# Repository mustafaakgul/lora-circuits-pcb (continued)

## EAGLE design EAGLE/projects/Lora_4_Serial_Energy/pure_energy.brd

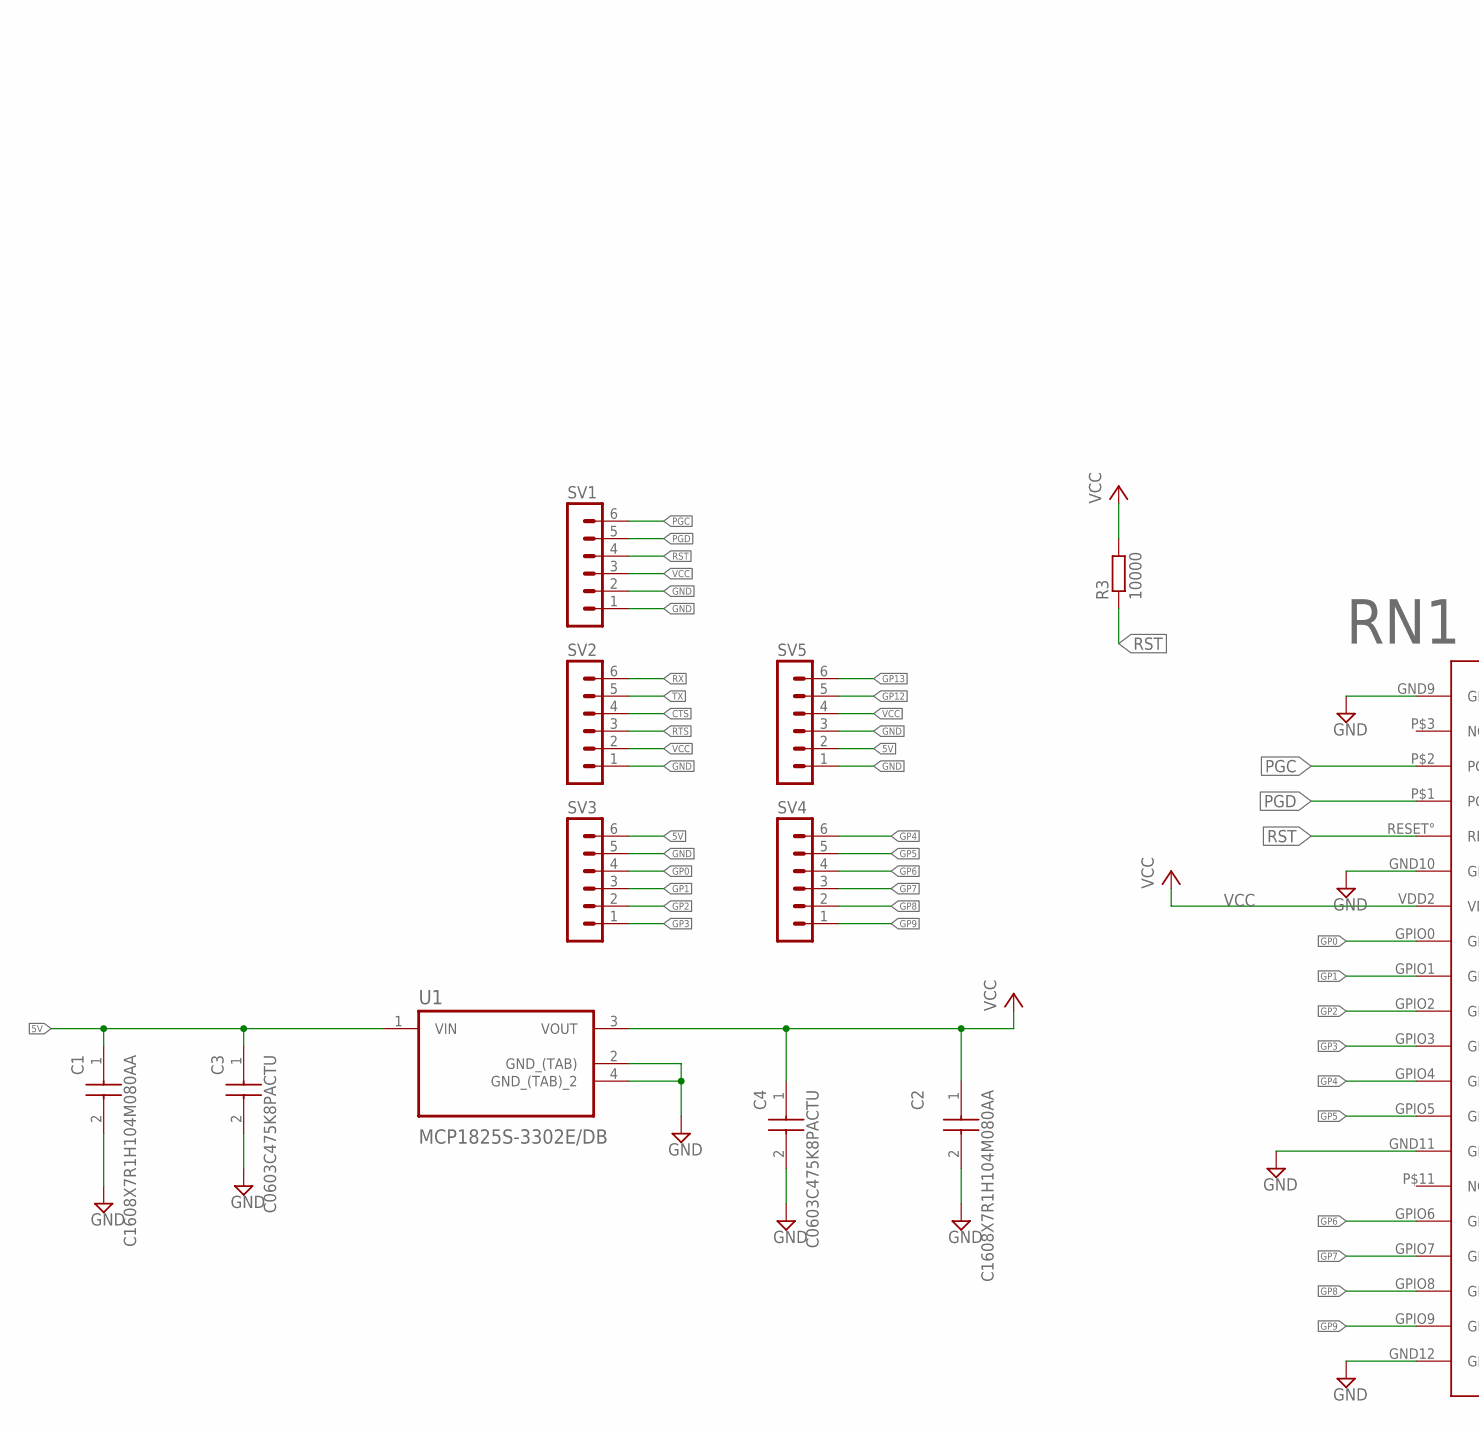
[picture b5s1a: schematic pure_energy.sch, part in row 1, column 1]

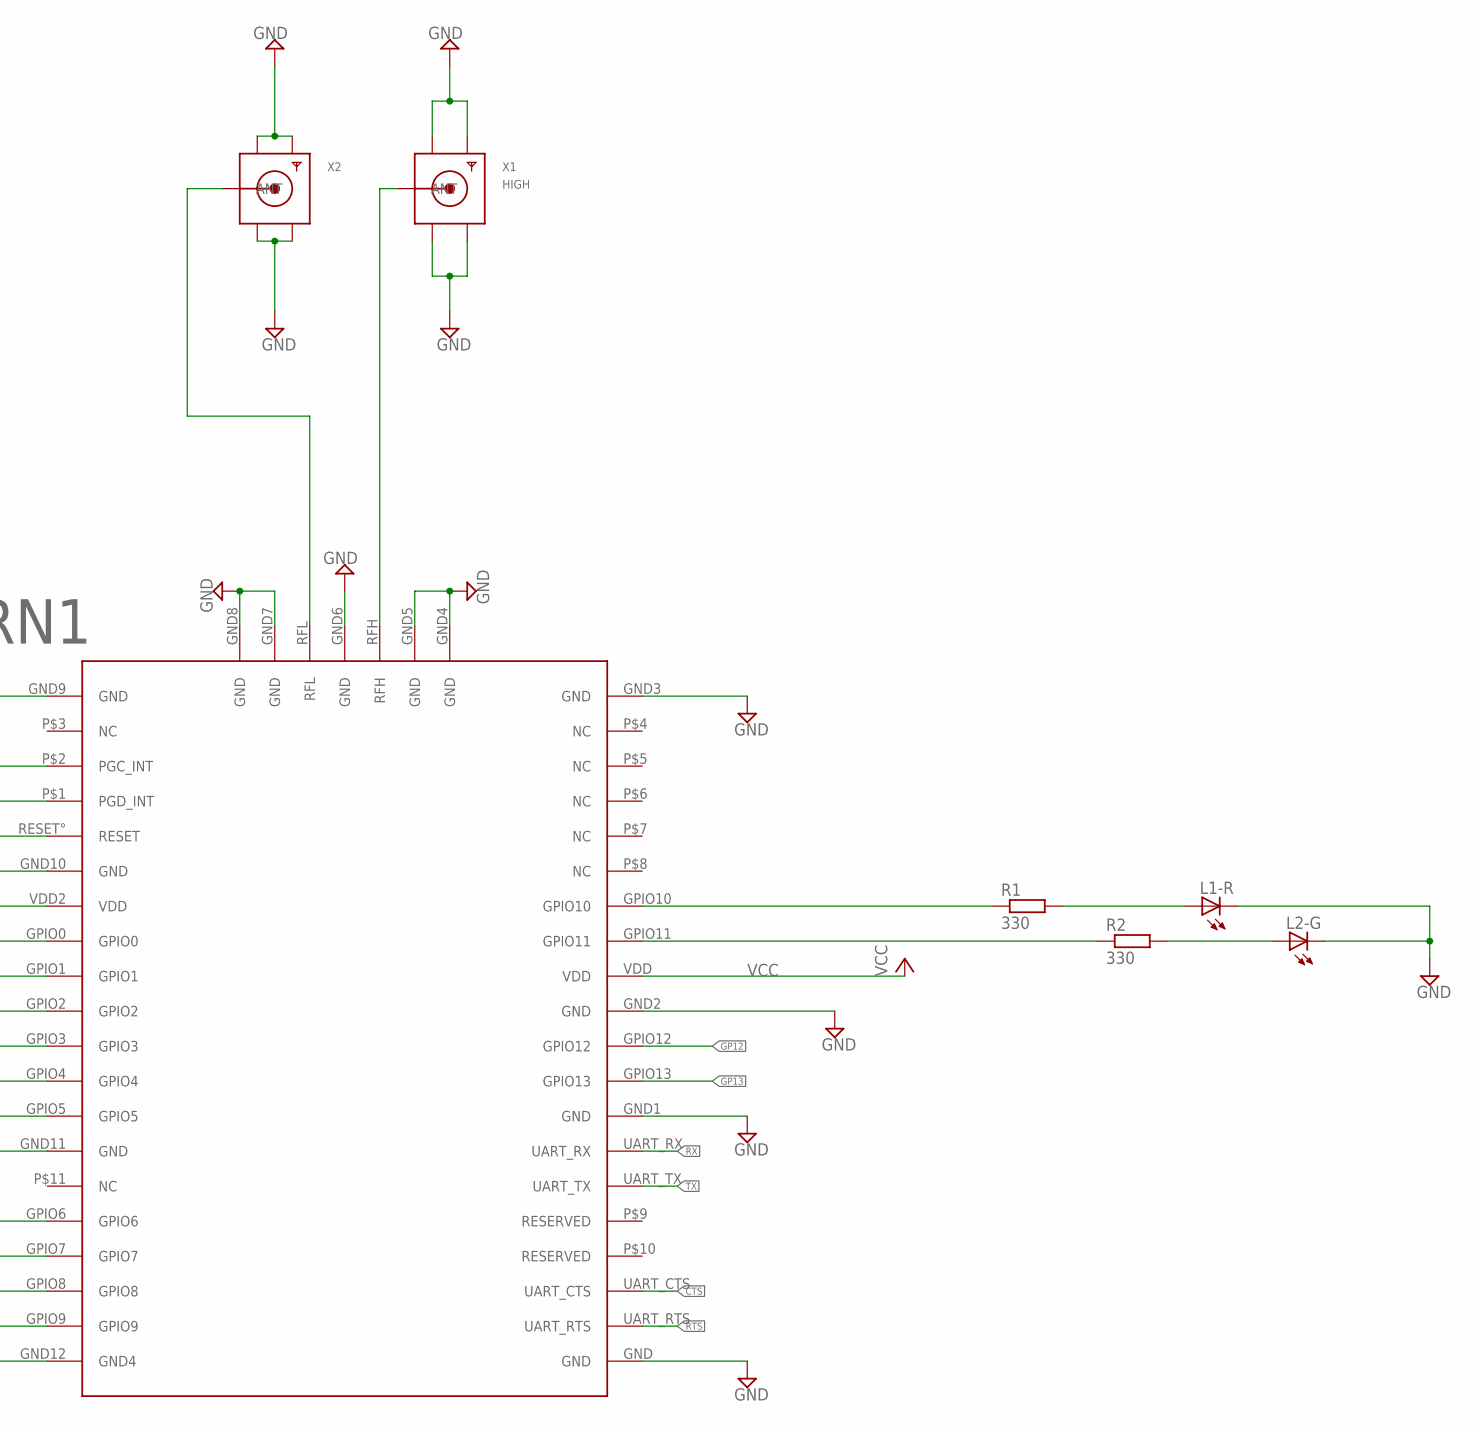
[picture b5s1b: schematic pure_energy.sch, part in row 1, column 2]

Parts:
C1, C2: C1608X7R1H104M080AA; CAPC1608X80N
C3, C4: C0603C475K8PACTU; CAPC1608X85N
L1-R, L2-G: LEDCHIP-LED0603; CHIP-LED0603
R1, R2: 330; R0603
R3: 10000; R0603
RN1: NEW_RN2483
SV1, SV2, SV3, SV4, SV5: MA06-1
U1: MCP1825S-3302E/DB; SOT230P700X180-4N
X1: HIGH; SMA_EDGELAUNCH
X2: SMACONNECTOR_EDGE; SMA_EDGELAUNCH

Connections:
5V: C1.1, C3.1 (C1), SV3.6, SV5.2, U1.1 (VIN)
CTS: RN1.UART_CTS, SV2.4
GND: C1.2, C2.2, C3.2 (C2), C4.2 (C2), L1-R.C, L2-G.C, RN1.GND, RN1.GND1 (GND), RN1.GND2 (GND), RN1.GND3 (GND), RN1.GND4 (GND), RN1.GND5 (GND), RN1.GND6 (GND), RN1.GND7 (GND), RN1.GND8 (GND), RN1.GND9 (GND), RN1.GND10 (GND), RN1.GND11 (GND), RN1.GND12 (GND4), SV1.1, SV1.2, SV2.1, SV3.5, SV5.1, SV5.3, U1.2 (GND_(TAB)), U1.4 (GND_(TAB)_2), X1.GND@1 (GND4), X1.GND@2 (GND3), X1.GND@3 (GND2), X1.GND@4 (GND1), X2.GND@1 (GND4), X2.GND@2 (GND3), X2.GND@3 (GND2), X2.GND@4 (GND1)
GP0: RN1.GPIO0, SV3.4
GP1: RN1.GPIO1, SV3.3
GP2: RN1.GPIO2, SV3.2
GP3: RN1.GPIO3, SV3.1
GP4: RN1.GPIO4, SV4.6
GP5: RN1.GPIO5, SV4.5
GP6: RN1.GPIO6, SV4.4
GP7: RN1.GPIO7, SV4.3
GP8: RN1.GPIO8, SV4.2
GP9: RN1.GPIO9, SV4.1
GP12: RN1.GPIO12, SV5.5
GP13: RN1.GPIO13, SV5.6
unnamed: RN1.RFL, X2.P (ANT)
unnamed: R1.1, RN1.GPIO10
unnamed: R2.1, RN1.GPIO11
unnamed: L1-R.A, R1.2
unnamed: L2-G.A, R2.2
unnamed: RN1.RFH, X1.P (ANT)
PGC: RN1.P$2 (PGC_INT), SV1.6
PGD: RN1.P$1 (PGD_INT), SV1.5
RST: R3.1, RN1.RESET° (RESET), SV1.4
RTS: RN1.UART_RTS, SV2.3
RX: RN1.UART_RX, SV2.6
TX: RN1.UART_TX, SV2.5
VCC: C2.1, C4.1 (C1), R3.2, RN1.VDD, RN1.VDD2 (VDD), SV1.3, SV2.2, SV5.4, U1.3 (VOUT)

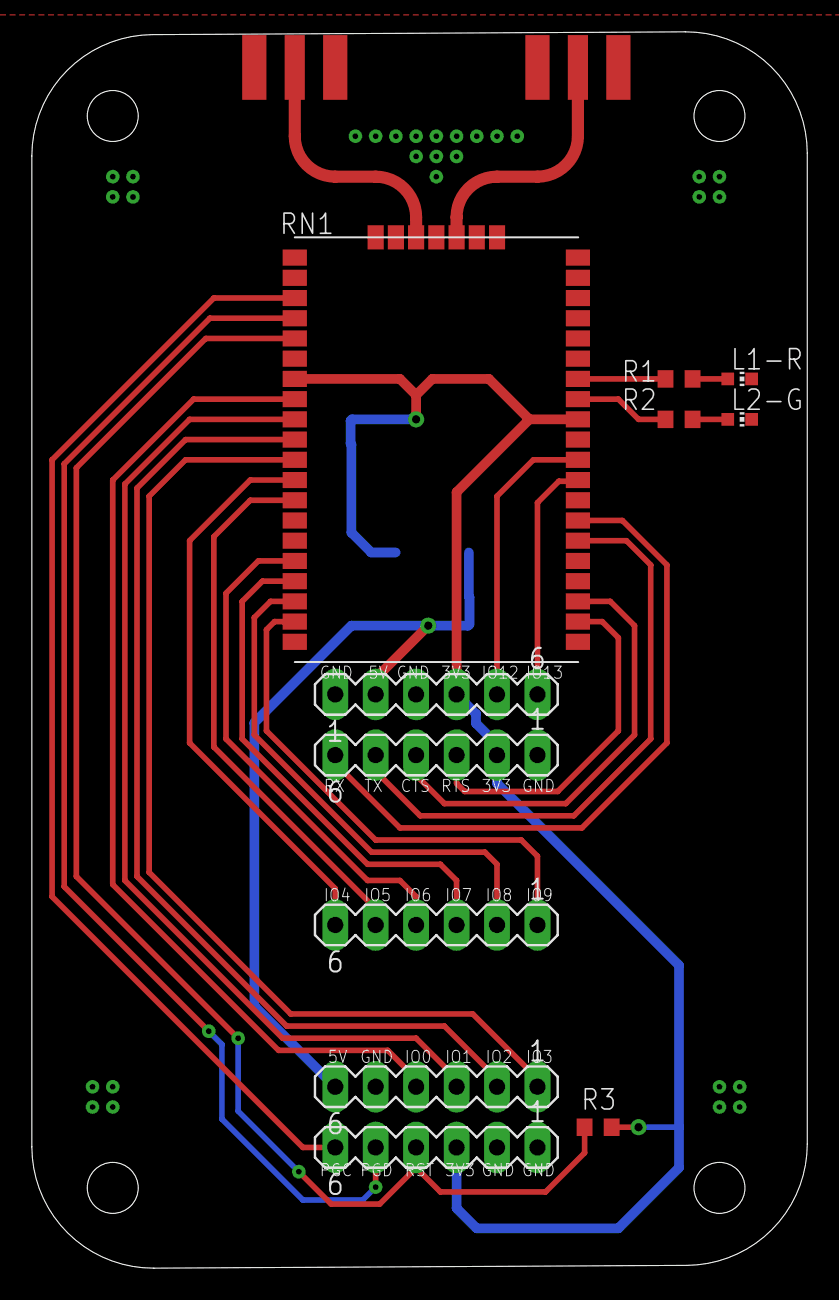
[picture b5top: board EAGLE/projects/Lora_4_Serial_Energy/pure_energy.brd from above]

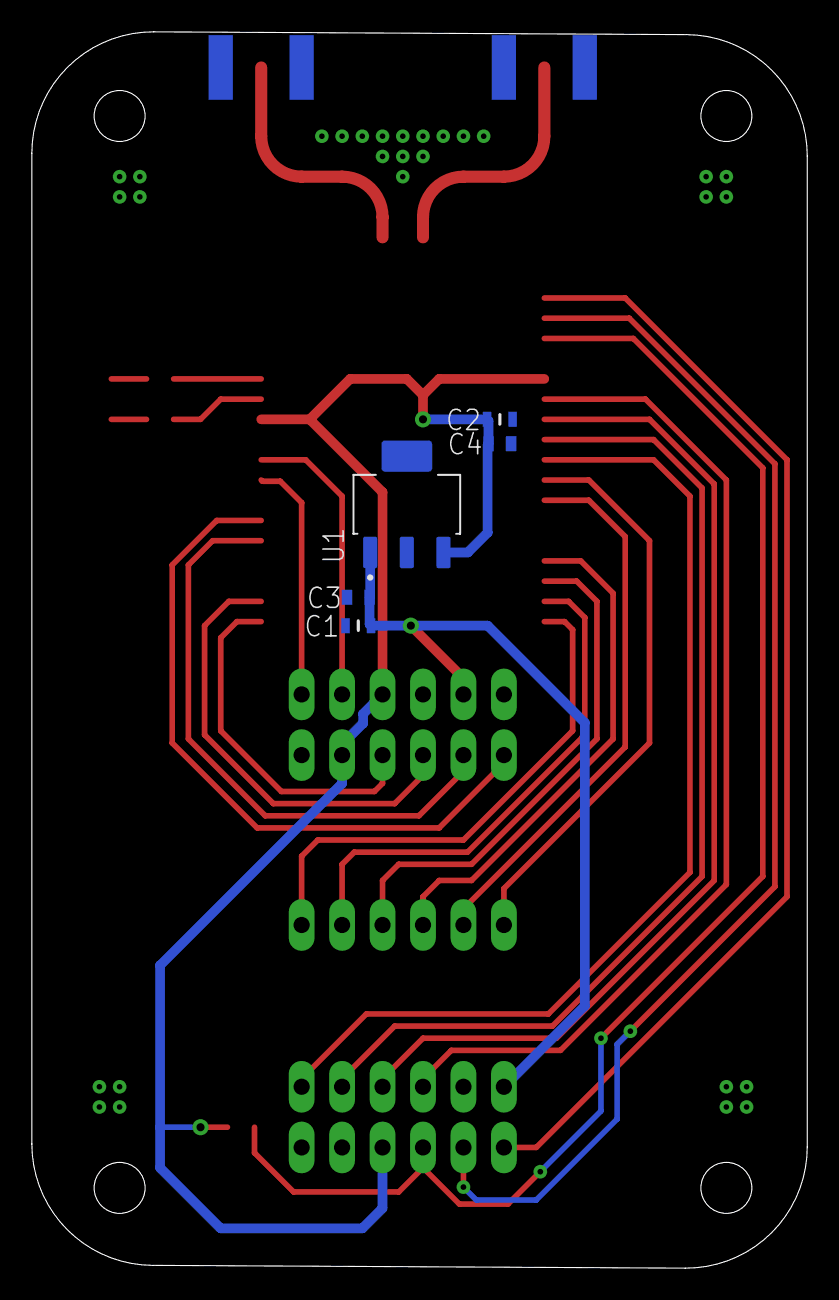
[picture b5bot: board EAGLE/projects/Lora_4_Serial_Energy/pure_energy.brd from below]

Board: 2 copper layers, 48.7 x 77.6 mm, 18 parts (5 on the bottom side), 28 nets.

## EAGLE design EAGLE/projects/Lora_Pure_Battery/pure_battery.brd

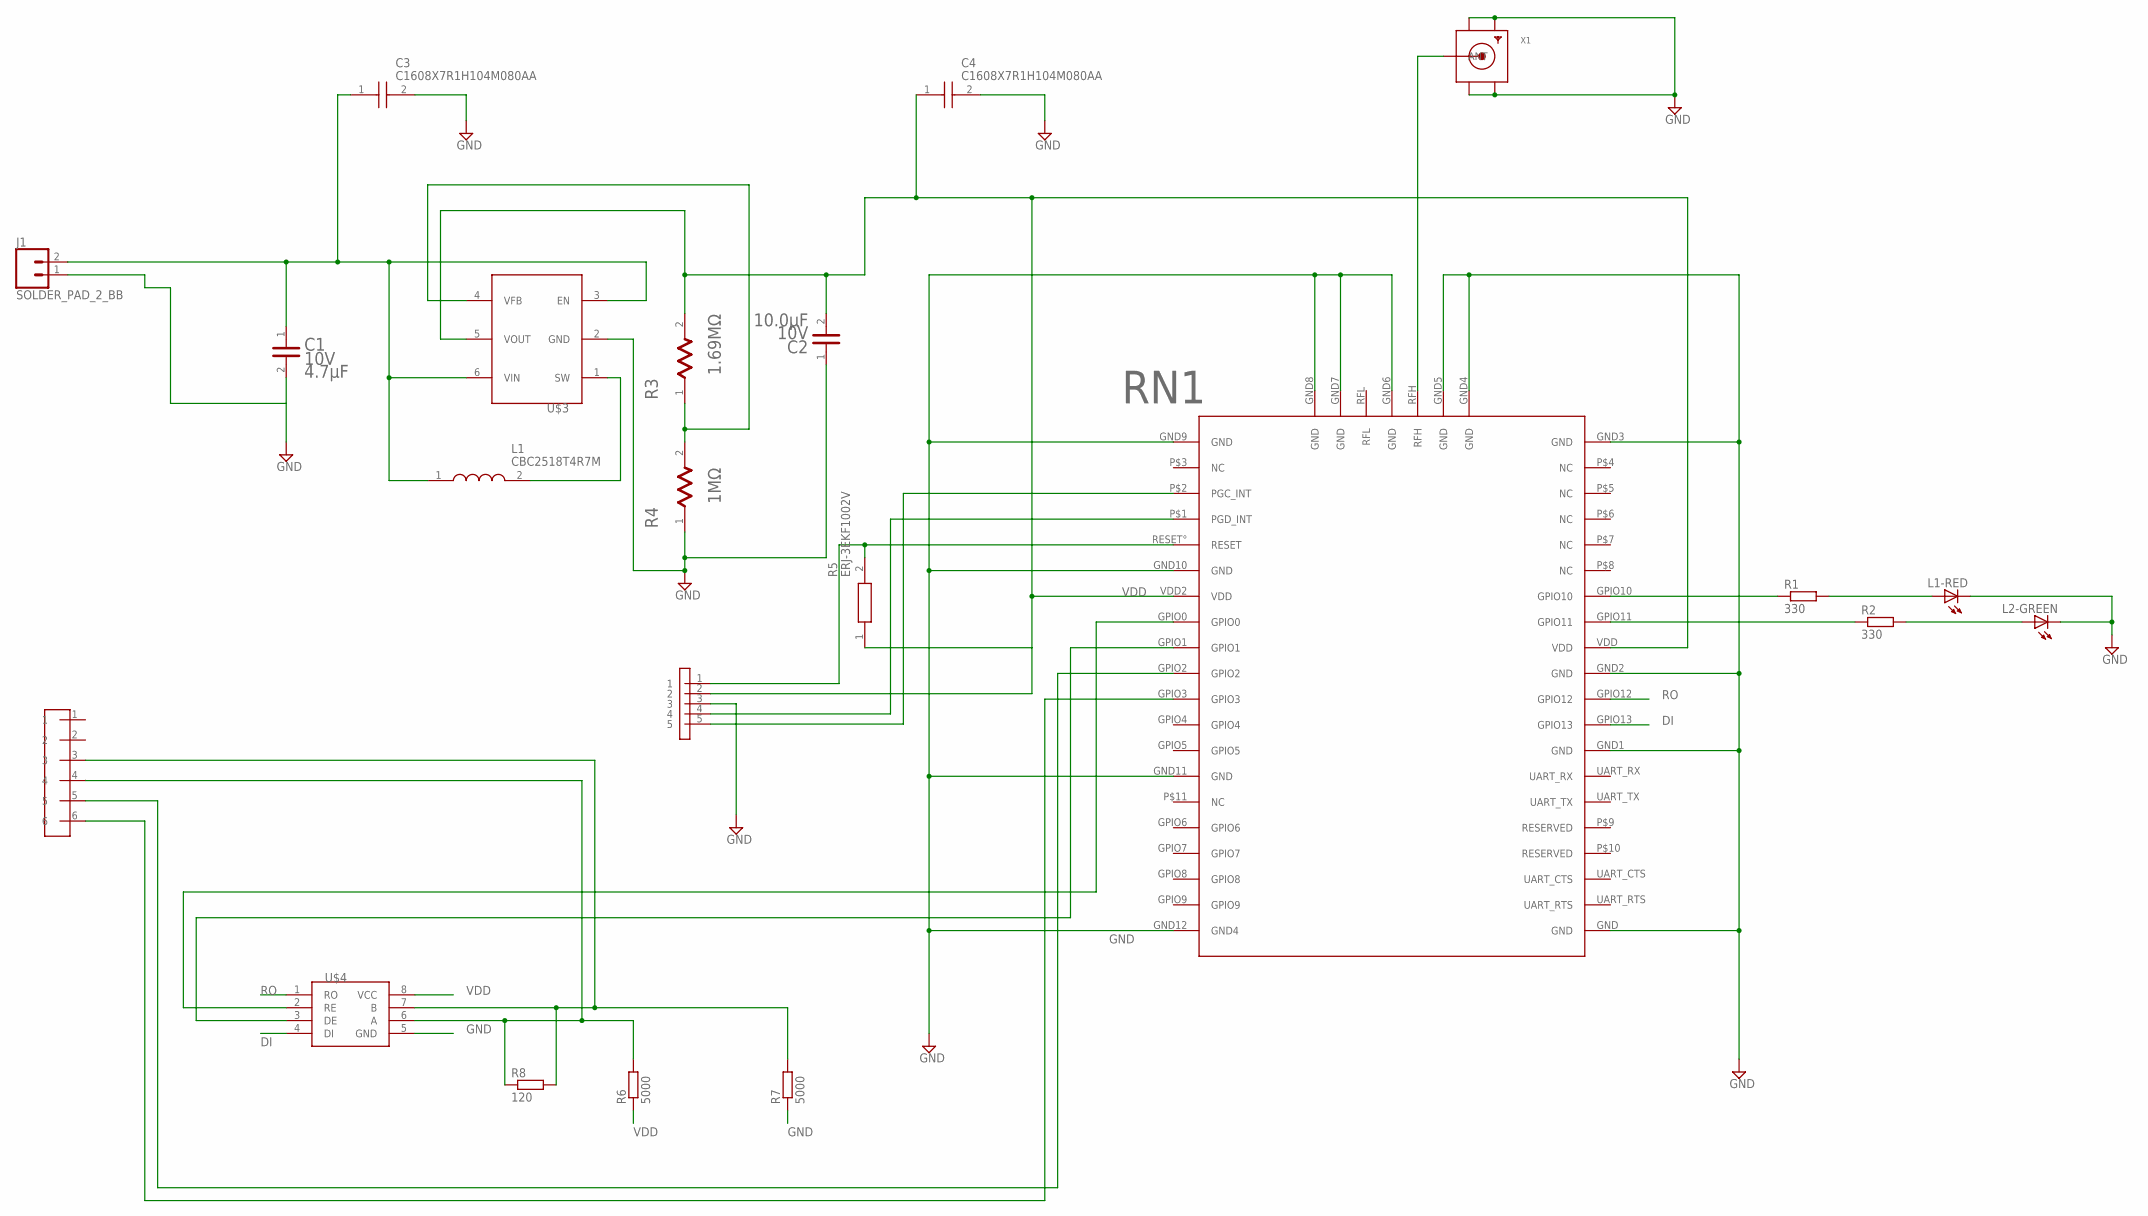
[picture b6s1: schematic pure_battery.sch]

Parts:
C1: KEMET_C0603C475K8PACTUKEMET_C0603C475K8PACTU_0_0; KEMET_C0603C475K8PACTU_0
C2: TDK_C1608X5R1A106M080ACTDK_C1608X5R1A106M080AC_0_0; TDK_C1608X5R1A106M080AC_0
C3, C4: C1608X7R1H104M080AA; CAPC1608X80N
J1: SOLDER_PAD_2_BB; SOLDER_PAD_2
L1: CBC2518T4R7M; INDC2518X200N
L1-RED, L2-GREEN: LEDCHIP-LED0603; CHIP-LED0603
R1, R2: 330; R0603
R3: VISHAY_CRCW06031M69FKEAVISHAY_CRCW06031M69FKEA_0_1; VISHAY_CRCW06031M69FKEA_1
R4: STACKPOLE_RMCF0603FT1M00STACKPOLE_RMCF0603FT1M00_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; STACKPOLE_RMCF0603FT1M00_1
R5: ERJ-3EKF1002V; RESC1608X55N
R6, R7: 5000; R0805
R8: 120; R0805
RN1: NEW_RN2483
U$1: CONNECTOR62; CONNECTOR6
U$2: ICSP52; ICSP
U$3: MCP16252
U$4: AMD3485E
X1: SMACONNECTOR_EDGE; SMA_EDGELAUNCH

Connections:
DI: RN1.GPIO13, U$4.4 (DI)
GND: C1.2, C2.1, C3.2, C4.2, J1.1, L1-RED.C, L2-GREEN.C, R4.1, R7.1, RN1.GND, RN1.GND1 (GND), RN1.GND2 (GND), RN1.GND3 (GND), RN1.GND4 (GND), RN1.GND5 (GND), RN1.GND6 (GND), RN1.GND7 (GND), RN1.GND8 (GND), RN1.GND9 (GND), RN1.GND10 (GND), RN1.GND11 (GND), RN1.GND12 (GND4), U$2.3, U$3.2 (GND), U$4.5 (GND), X1.GND@1 (GND4), X1.GND@2 (GND3), X1.GND@3 (GND2), X1.GND@4 (GND1)
unnamed: R1.1, RN1.GPIO10
unnamed: L1-RED.A, R1.2
unnamed: C1.1, C3.1, J1.2, L1.1, U$3.3 (EN), U$3.6 (VIN)
unnamed: R2.1, RN1.GPIO11
unnamed: L2-GREEN.A, R2.2
unnamed: RN1.P$2 (PGC_INT), U$2.5
unnamed: L1.2, U$3.1 (SW)
unnamed: R3.1, R4.2, U$3.4 (VFB)
unnamed: RN1.P$1 (PGD_INT), U$2.4
unnamed: RN1.GPIO0, U$4.2 (RE)
unnamed: R5.2, RN1.RESET° (RESET), U$2.1
unnamed: RN1.RFH, X1.P (ANT)
unnamed: R7.2, R8.2, U$1.3, U$4.7 (B)
unnamed: R6.2, R8.1, U$1.4, U$4.6 (A)
unnamed: RN1.GPIO1, U$4.3 (DE)
unnamed: RN1.GPIO2, U$1.5
unnamed: RN1.GPIO3, U$1.6
RO: RN1.GPIO12, U$4.1 (RO)
VDD: C2.2, C4.1, R3.2, R5.1, R6.1, RN1.VDD, RN1.VDD2 (VDD), U$2.2, U$3.5 (VOUT), U$4.8 (VCC)

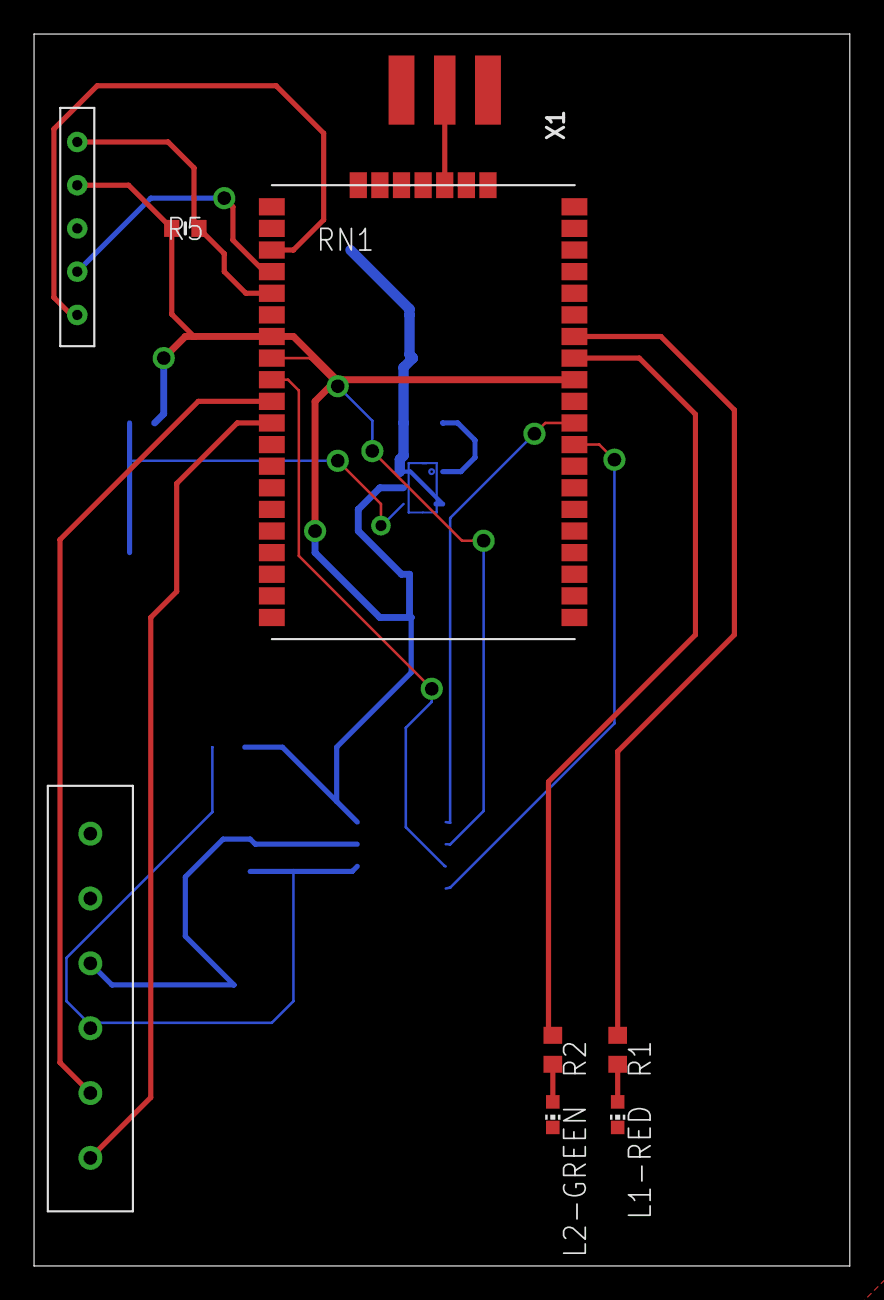
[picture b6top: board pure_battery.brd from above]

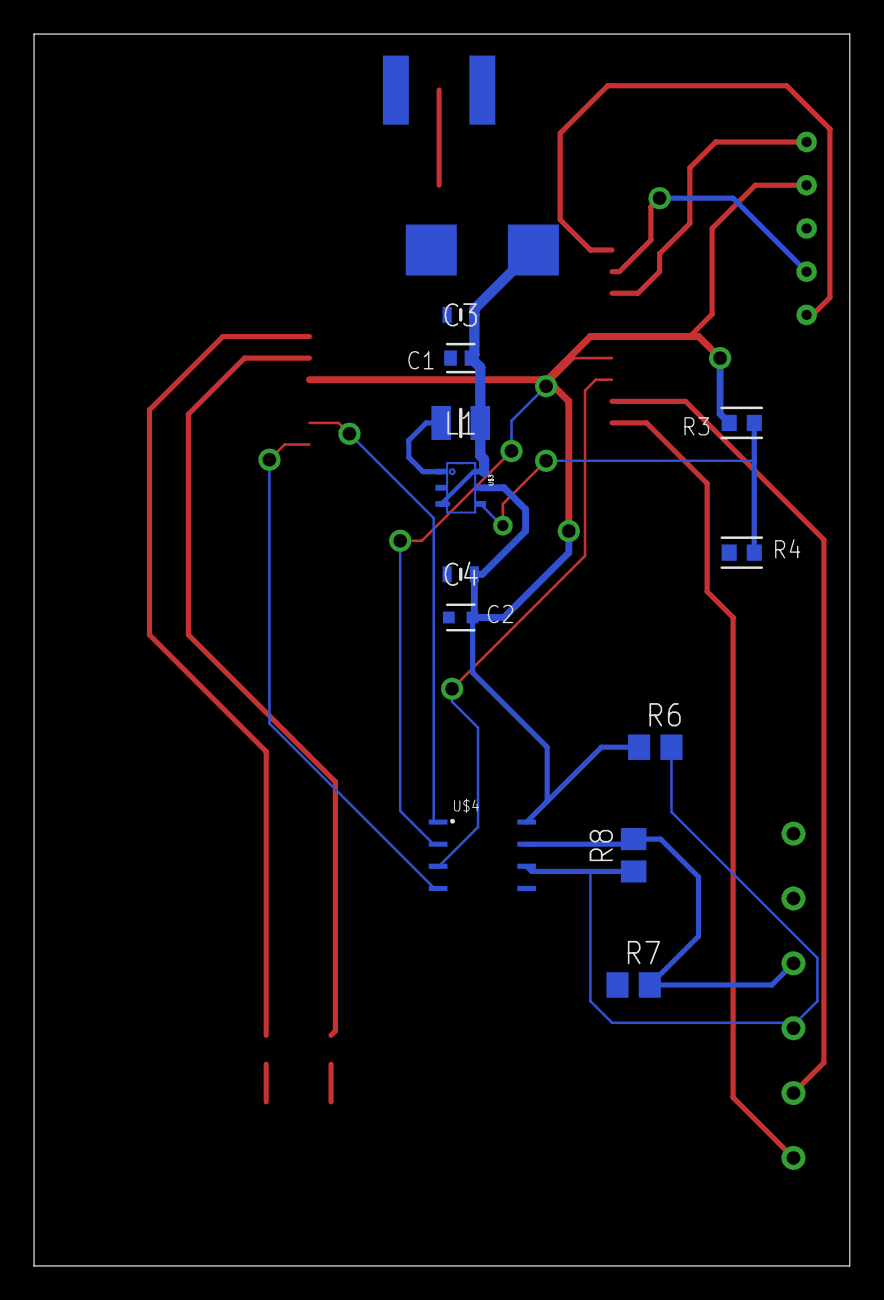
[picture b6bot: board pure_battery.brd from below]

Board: 2 copper layers, 47.9 x 72.4 mm, 22 parts (13 on the bottom side), 21 nets.

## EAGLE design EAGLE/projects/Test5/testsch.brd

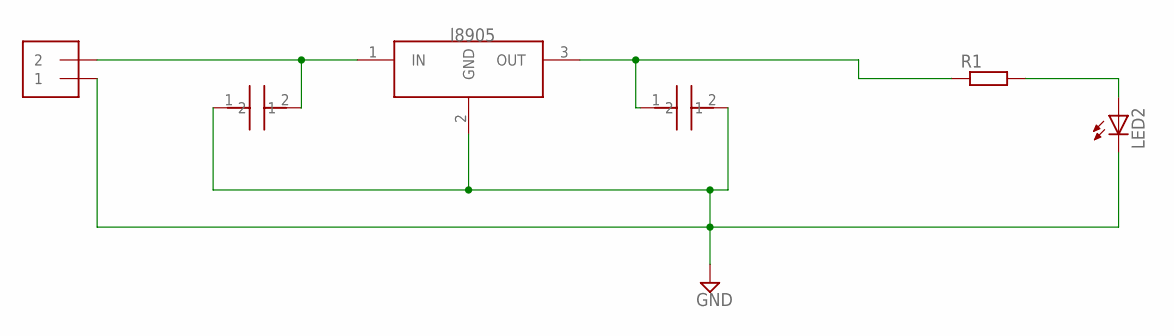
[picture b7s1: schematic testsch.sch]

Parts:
J1: 1X2-3.5MM
LED2: LEDSMT1206; 1206
R1: R-EU_M1206; M1206
U$1: L7805TESTA; L7805
U$2, U$3: 0.33UF_CUSTOM; C1206

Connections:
GND: J1.1, LED2.C, U$1.2 (GND), U$2.1, U$3.2
unnamed: J1.2, U$1.1 (IN), U$2.2
unnamed: LED2.A, R1.2
unnamed: R1.1, U$1.3 (OUT), U$3.1

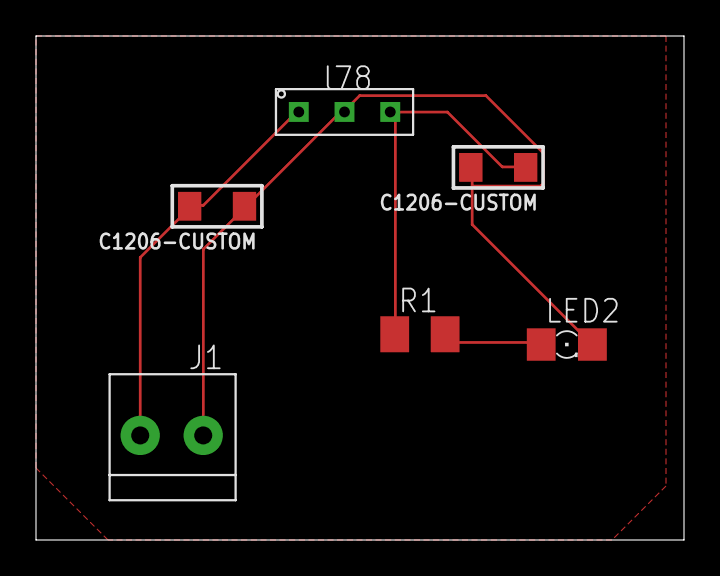
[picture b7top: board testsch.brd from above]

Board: 2 copper layers, 36.0 x 28.0 mm, 6 parts (0 on the bottom side), 4 nets.

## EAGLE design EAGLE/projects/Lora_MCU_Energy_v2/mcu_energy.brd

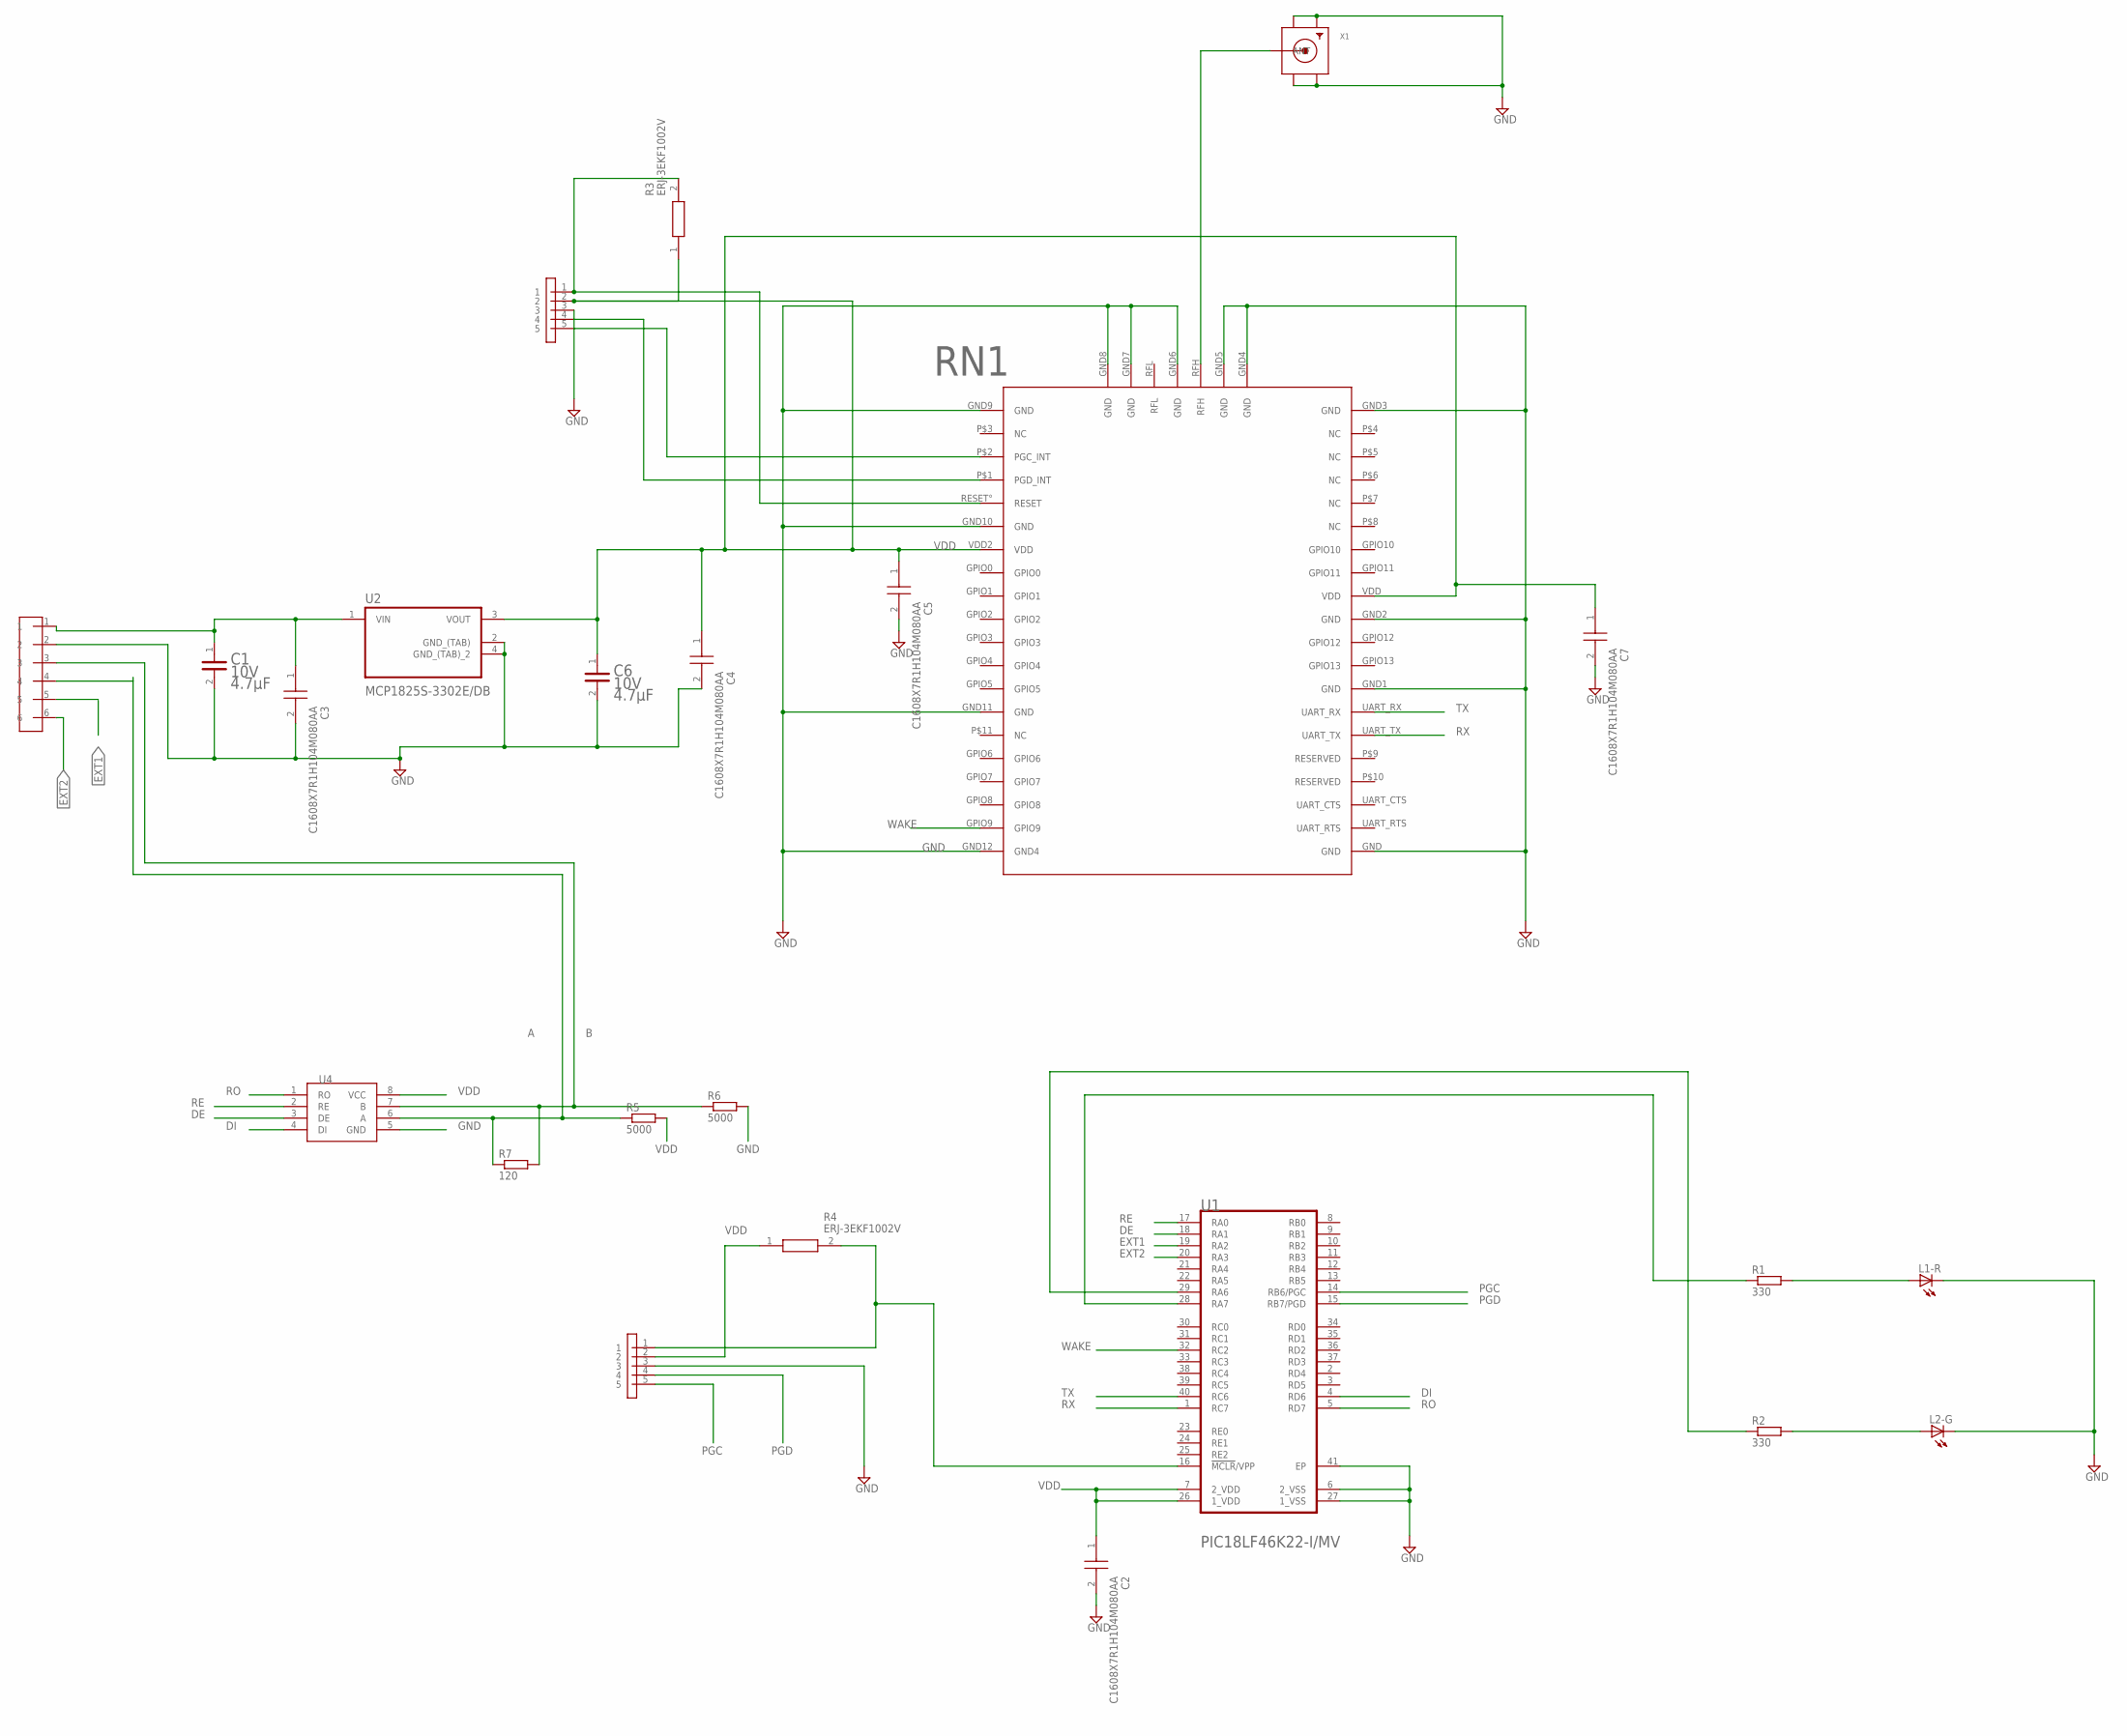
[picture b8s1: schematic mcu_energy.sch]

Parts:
C1, C6: KEMET_C0603C475K8PACTUKEMET_C0603C475K8PACTU_0_0; KEMET_C0603C475K8PACTU_0
C2, C3, C4, C5, C7: C1608X7R1H104M080AA; CAPC1608X80N
L1-R, L2-G: LEDCHIP-LED0603; CHIP-LED0603
R1, R2: 330; R0603
R3, R4: ERJ-3EKF1002V; RESC1608X55N
R5, R6: 5000; R0805
R7: 120; R0805
RN1: NEW_RN2483
U1: MICROCHIP_PIC18LF46K22-I-MVMICROCHIP_PIC18LF46K22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; MICROCHIP_PIC18LF46K22-I-MV_1
U2: MCP1825S-3302E/DB; SOT230P700X180-4N
U4: AMD3485E
U6: CONNECTOR6_V2
U$2: ICSP52; ICSP
U$3: ICSP_V2
X1: SMACONNECTOR_EDGE; SMA_EDGELAUNCH

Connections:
A: R5.1, R7.1, U4.6 (A), U6.4
B: R6.1, R7.2, U4.7 (B), U6.3
DE: U1.18 (RA1), U4.3 (DE)
DI: U1.4 (RD6), U4.4 (DI)
EXT1: U1.19 (RA2), U6.5
EXT2: U1.20 (RA3), U6.6
GND: C1.2, C2.2, C3.2, C4.2, C5.2, C6.2, C7.2, L1-R.C, L2-G.C, R6.2, RN1.GND, RN1.GND1 (GND), RN1.GND2 (GND), RN1.GND3 (GND), RN1.GND4 (GND), RN1.GND5 (GND), RN1.GND6 (GND), RN1.GND7 (GND), RN1.GND8 (GND), RN1.GND9 (GND), RN1.GND10 (GND), RN1.GND11 (GND), RN1.GND12 (GND4), U1.6 (2_VSS), U1.27 (1_VSS), U1.41 (EP), U2.2 (GND_(TAB)), U2.4 (GND_(TAB)_2), U4.5 (GND), U6.2, U$2.3, U$3.3, X1.GND@1 (GND4), X1.GND@2 (GND3), X1.GND@3 (GND2), X1.GND@4 (GND1)
unnamed: L1-R.A, R1.2
unnamed: L2-G.A, R2.2
unnamed: R2.1, U1.29 (RA6)
unnamed: R1.1, U1.28 (RA7)
unnamed: C1.1, C3.1, U2.1 (VIN), U6.1
unnamed: RN1.P$2 (PGC_INT), U$3.5
unnamed: R4.2, U1.16 (!MCLR!/VPP), U$2.1
unnamed: RN1.P$1 (PGD_INT), U$3.4
unnamed: R3.2, RN1.RESET° (RESET), U$3.1
unnamed: RN1.RFH, X1.P (ANT)
PGC: U1.14 (RB6/PGC), U$2.5
PGD: U1.15 (RB7/PGD), U$2.4
RE: U1.17 (RA0), U4.2 (RE)
RO: U1.5 (RD7), U4.1 (RO)
RX: RN1.UART_TX, U1.1 (RC7)
TX: RN1.UART_RX, U1.40 (RC6)
VDD: C2.1, C4.1, C5.1, C6.1, C7.1, R3.1, R4.1, R5.2, RN1.VDD, RN1.VDD2 (VDD), U1.7 (2_VDD), U1.26 (1_VDD), U2.3 (VOUT), U4.8 (VCC), U$2.2, U$3.2
WAKE: RN1.GPIO9, U1.32 (RC2)

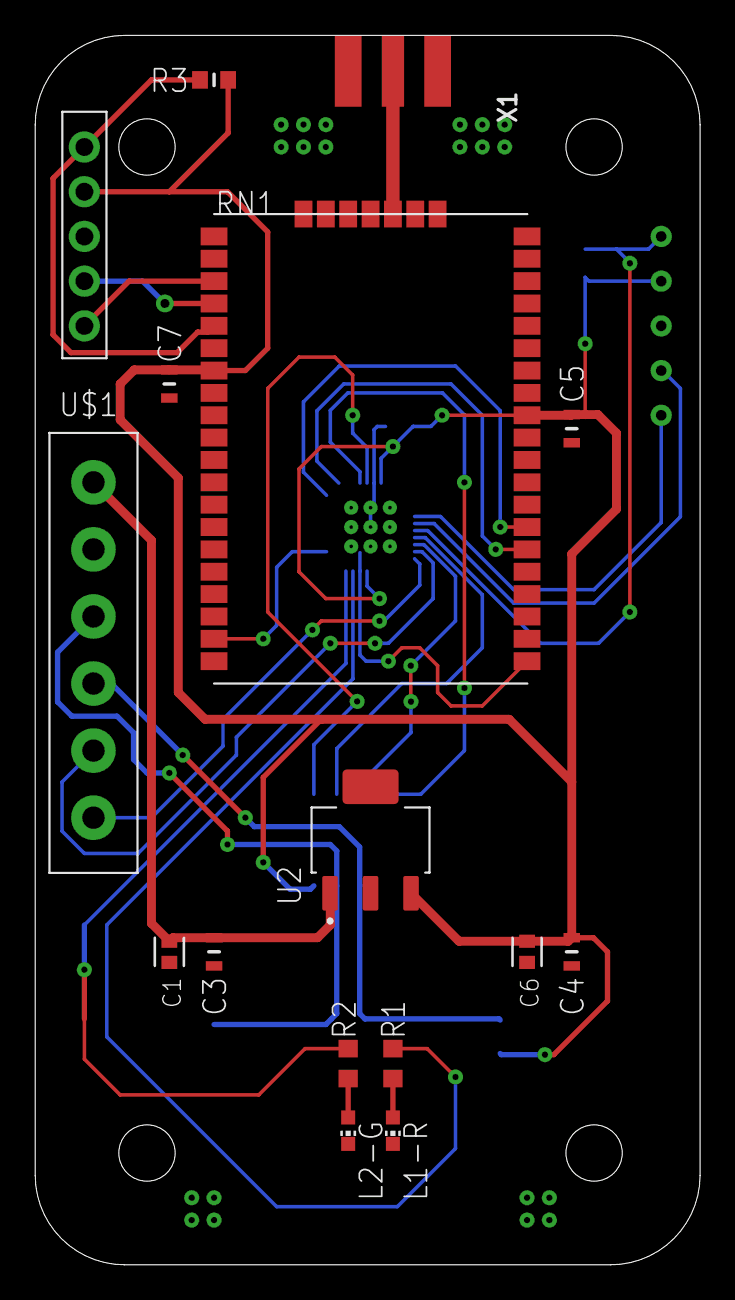
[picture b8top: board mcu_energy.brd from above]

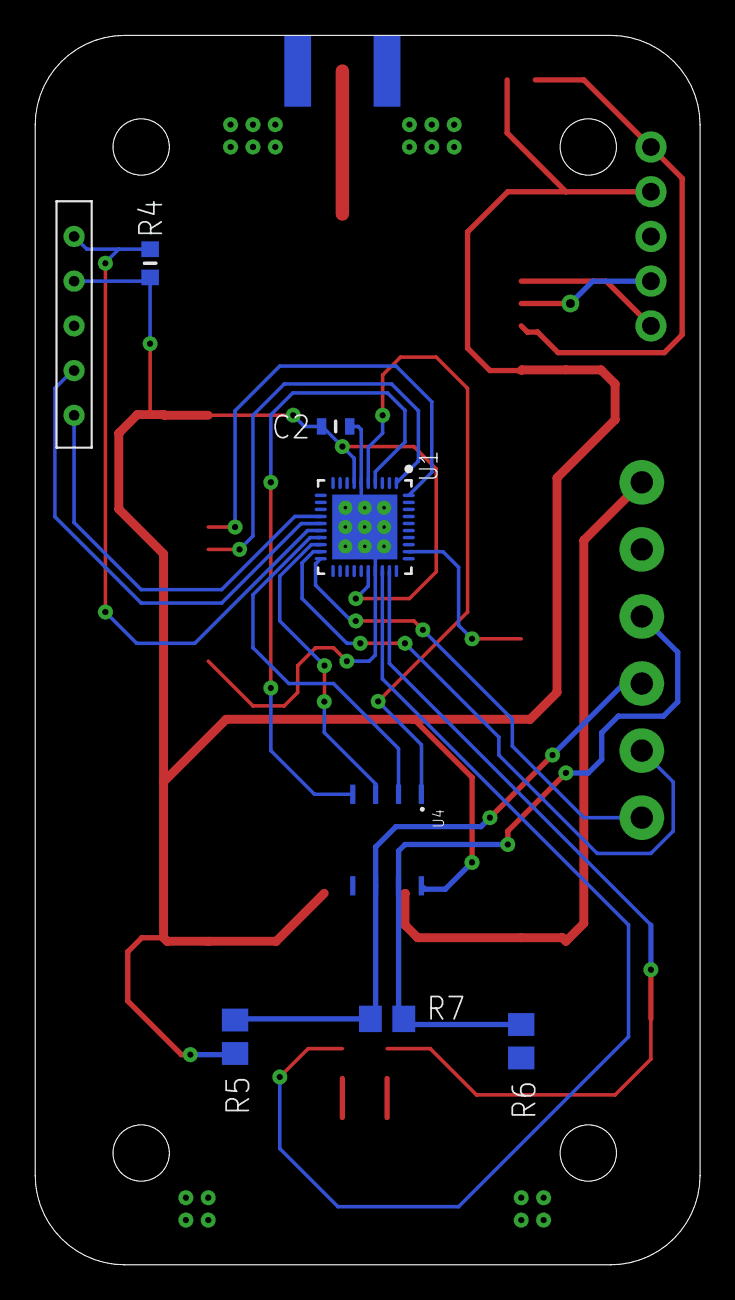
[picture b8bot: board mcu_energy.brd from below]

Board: 2 copper layers, 37.8 x 69.8 mm, 24 parts (8 on the bottom side), 25 nets.

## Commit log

2023-12-11 add all
2024-04-10 Create LICENSE
